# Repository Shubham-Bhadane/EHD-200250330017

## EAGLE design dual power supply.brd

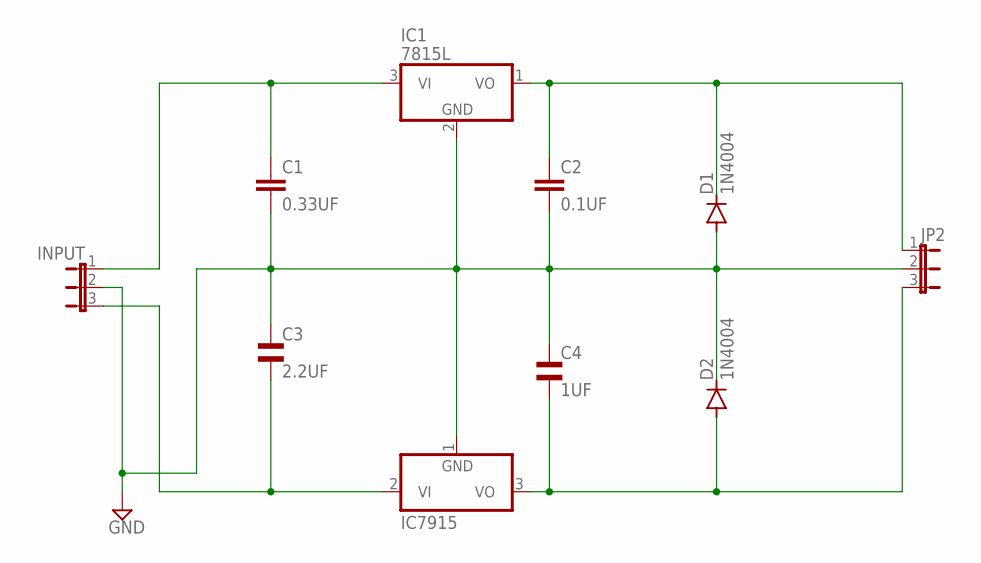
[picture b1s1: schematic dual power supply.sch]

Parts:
C1: 0.33UF; C2.5-2
C2: 0.1UF; C2.5-2
C3: 2.2UF; EU25-10
C4: 1UF; EU25-10
D1, D2: 1N4004; DO41-10
IC1: 7815L; TO92
IC7915: 7915L; TO92
INPUT: JP2E; JP2
JP2: JP2E; JP2

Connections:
IC7815: C1.2, C2.2, C3.1, C4.1, D1.A, D2.C, IC1.2 (GND), IC7915.1 (GND), INPUT.2, JP2.2; also elsewhere on the board
unnamed: C2.1, D1.C, IC1.1 (VO), JP2.1
unnamed 3: C3.2, IC7915.2 (VI), INPUT.3; also elsewhere on the board
unnamed: C1.1, IC1.3 (VI), INPUT.1
unnamed 5: C4.2, D2.A, IC7915.3 (VO), JP2.3; also elsewhere on the board

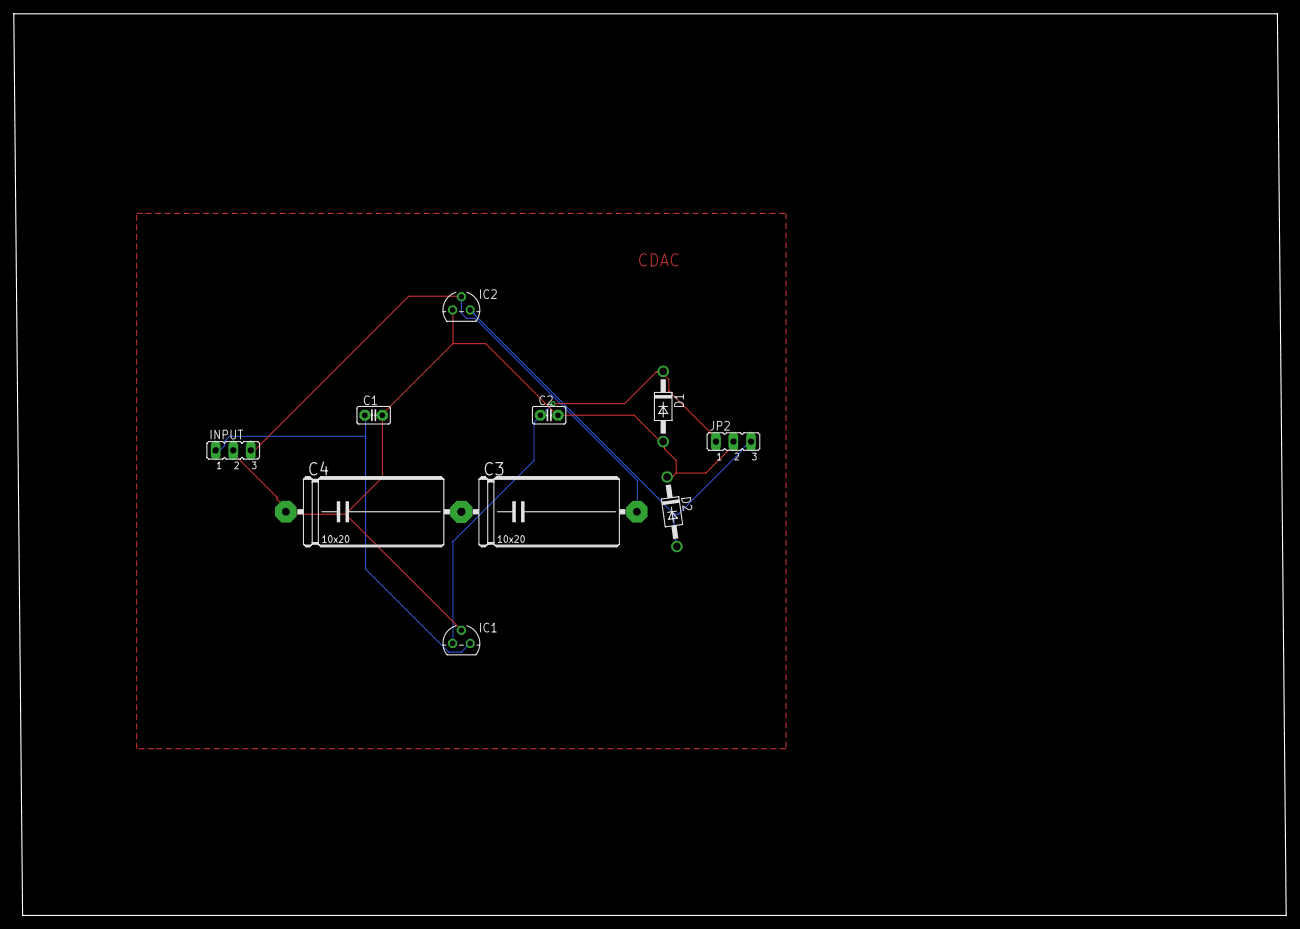
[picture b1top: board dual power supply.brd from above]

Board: 2 copper layers, 184.1 x 130.5 mm, 10 parts (0 on the bottom side), 5 nets.

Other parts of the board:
IC2: TO92

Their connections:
IC7815: IC2.1; also elsewhere on the board
unnamed 3: IC2.2; also elsewhere on the board
unnamed 5: IC2.3; also elsewhere on the board

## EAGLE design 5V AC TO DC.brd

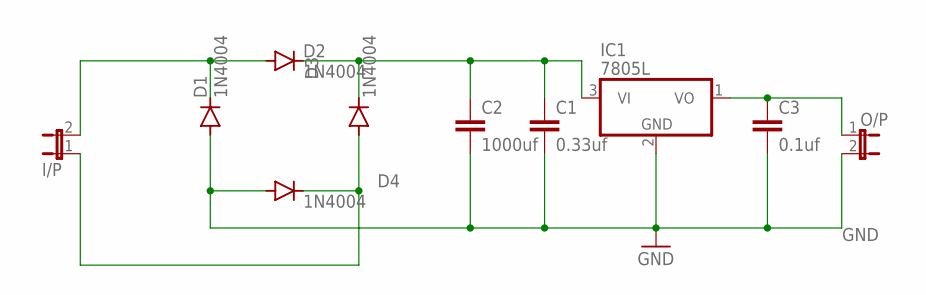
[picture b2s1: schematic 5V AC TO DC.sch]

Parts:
C1: 0.33uf; C2.5-3
C2: 1000uf; C2.5-3
C3: 0.1uf; C2.5-3
D1, D2, D3, D4: 1N4004; DO41-10
I/P: JP1E; JP1
IC1: 7805L; TO92
O/P: JP1E; JP1

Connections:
GND: C1.2, C2.2, C3.2, D1.A, D4.A, IC1.2 (GND), O/P.2
unnamed: D1.C, D2.A, I/P.2
unnamed: C1.1, C2.1, D2.C, D3.C, IC1.3 (VI)
unnamed: C3.1, IC1.1 (VO), O/P.1
unnamed: D3.A, D4.C, I/P.1

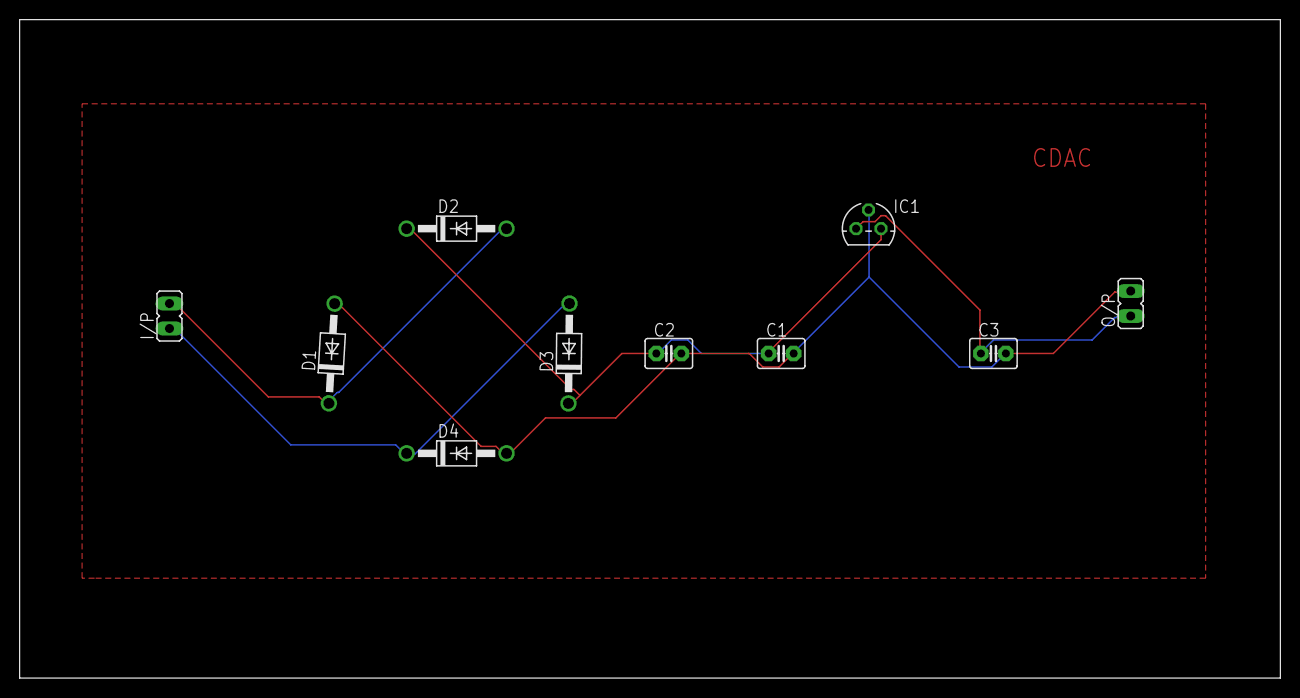
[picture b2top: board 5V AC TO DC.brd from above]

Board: 2 copper layers, 128.2 x 67.0 mm, 10 parts (0 on the bottom side), 5 nets.
